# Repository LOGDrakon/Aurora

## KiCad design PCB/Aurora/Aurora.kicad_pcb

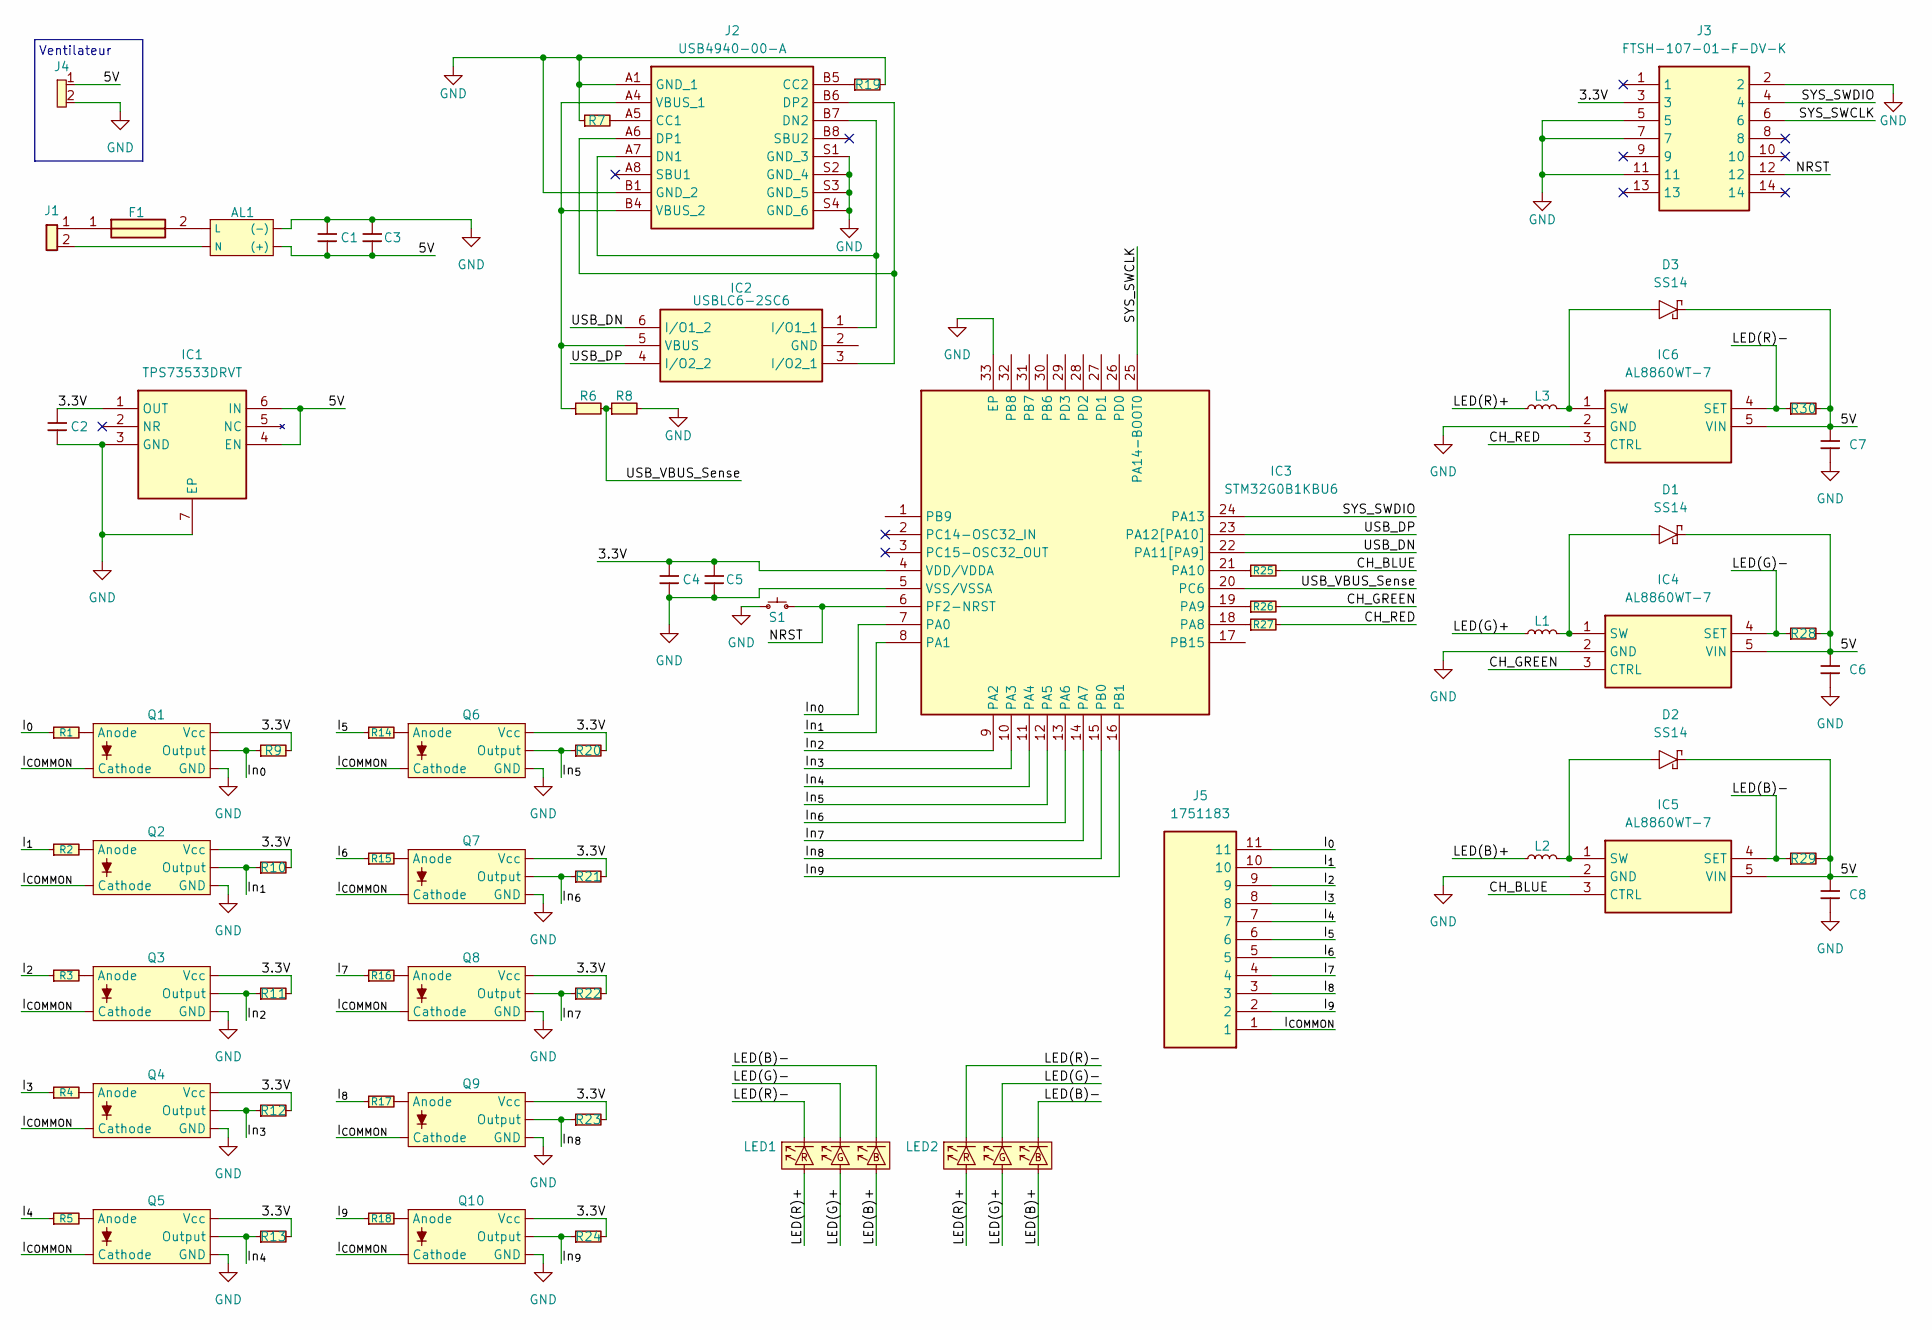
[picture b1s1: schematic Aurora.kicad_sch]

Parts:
AL1: PSK-10E-5; Parts Reference PSK-10E-5; Mouser No 490-PSK-10E-5
C1, C2, C4: GXT21BR71A475KE13L; CAPC2012X140N; Manufacturer_Part_Number GXT21BR71A475KE13L
C3: 100nF; C_0402_1005Metric; Parts Reference AC0402KRX7R7BB104
C5: 100nF; C_0402_1005Metric
C6, C7, C8: CGA4J1X7R0J106K125AC; CGA4J2NP01H223J125AA; Mouser Part Number 810-CGA4J1X7R0J106K
D1, D2, D3: SS14; DIOM5227X270N; Mouser Part Number 512-SS14
F1: 3403.0166.24; 3403016624; Mouser Part Number 693-3403.0166.24
IC1: TPS73533DRVT; SON65P200X200X80-7N; Mouser Part Number 595-TPS73533DRVT
IC2: USBLC6-2SC6; SOT95P280X145-6N; Mouser Part Number 511-USBLC6-2SC6
IC3: STM32G0B1KBU6; QFN-32-1EP_5x5mm_P0.5mm_EP3.45x3.45mm
IC4, IC5, IC6: AL8860WT-7; SOT95P280X100-5N; Mouser Part Number 621-AL8860WT-7
J1: 1190297; Mouser Part Number 651-1190297
J2: USB4940-00-A; USB494000A; Manufacturer_Part_Number USB4940-00-A
J3: FTSH-107-01-F-DV-K; FTSH-107-XX-YYY-DV-K; Mouser Part Number 200-FTSH10701FDVK
J4: 1190297; Pad_Connector_2; Mouser Part Number 651-1190297
J5: 1751183; Mouser Part Number 651-1751183
L1, L2, L3: PA4332.472NLT; PA4332472NLT; Mouser Part Number 673-PA4332472NLT
LED1, LED2: OT-3RGB-C30
Q1, Q2, Q3, Q4, Q5, Q6, Q7, Q8, Q9, Q10: TLP2303TPLE; Parts Reference TLP2303TPLE; Mouser No 757-TLP2303TPLE
R1, R2, R3, R4, R5, R14, R15, R16, R17, R18: 5.1R; RESC5025X120N; Mouser Part Number 279-35025K1FT
R6: MCT0603MC3302FP500; RESC1608X55N; Mouser Part Number 594-MCT0603MC3302FP5
R7, R19: CR0603-FX-5101ELF; RESC1608X55N; Mouser Part Number 652-CR0603FX-5101ELF
R8: ERJ-P08F8202V; ERJP08__1206_; Mouser Part Number 667-ERJ-P08F8202V
R9, R10, R11, R12, R13, R20, R21, R22, R23, R24: 3.3R; RESC1608X55N; Mouser Part Number 652-CR0603-FX3301ELF
R25, R26, R27: 100R; R_0603_1608Metric; Parts Reference SFR03EZPJ101; Mouser No 755-SFR03EZPJ101
R28, R29, R30: 0.16R; R_0603_1608Metric; Parts Reference RL0603FR-070R16L; Mouser No 603-RL0603FR-070R16L
S1: SPST; TS09-63-25-WT-160-SMT-TR; Parts Reference TS09-63-25-WT-160-SMT-TR; Mouser No 179-TS0925WT160SMTTR

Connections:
/3.3V: C2.1, C4.1, C5.1, IC1.1 (OUT), IC3.4 (VDD/VDDA), J3.3, Q1.6 (Vcc), Q2.6 (Vcc), Q3.6 (Vcc), Q4.6 (Vcc), Q5.6 (Vcc), Q6.6 (Vcc), Q7.6 (Vcc), Q8.6 (Vcc), Q9.6 (Vcc), Q10.6 (Vcc), R9.2, R10.2, R11.2, R12.2, R13.2, R20.2, R21.2, R22.2, R23.2, R24.2
/5V: AL1.4 ((+)), C1.2, C3.2, C6.1, C7.1, C8.1, D1.1, D2.1, D3.1, IC1.4 (EN), IC1.6 (IN), IC4.5 (VIN), IC5.5 (VIN), IC6.5 (VIN), J4.1, R28.2, R29.2, R30.2
/CH_BLUE: IC5.3 (CTRL), R25.2
/CH_GREEN: IC4.3 (CTRL), R26.2
/CH_RED: IC6.3 (CTRL), R27.2
/I_{0}: J5.11, R1.1
/I_{1}: J5.10, R2.1
/I_{2}: J5.9, R3.1
/I_{3}: J5.8, R4.1
/I_{4}: J5.7, R5.1
/I_{5}: J5.6, R14.1
/I_{6}: J5.5, R15.1
/I_{7}: J5.4, R16.1
/I_{8}: J5.3, R17.1
/I_{9}: J5.2, R18.1
/I_{COMMON}: J5.1, Q1.3 (Cathode), Q2.3 (Cathode), Q3.3 (Cathode), Q4.3 (Cathode), Q5.3 (Cathode), Q6.3 (Cathode), Q7.3 (Cathode), Q8.3 (Cathode), Q9.3 (Cathode), Q10.3 (Cathode)
/In_{0}: IC3.7 (PA0), Q1.5 (Output), R9.1
/In_{1}: IC3.8 (PA1), Q2.5 (Output), R10.1
/In_{2}: IC3.9 (PA2), Q3.5 (Output), R11.1
/In_{3}: IC3.10 (PA3), Q4.5 (Output), R12.1
/In_{4}: IC3.11 (PA4), Q5.5 (Output), R13.1
/In_{5}: IC3.12 (PA5), Q6.5 (Output), R20.1
/In_{6}: IC3.13 (PA6), Q7.5 (Output), R21.1
/In_{7}: IC3.14 (PA7), Q8.5 (Output), R22.1
/In_{8}: IC3.15 (PB0), Q9.5 (Output), R23.1
/In_{9}: IC3.16 (PB1), Q10.5 (Output), R24.1
/LED(B)+: L2.1, LED1.6, LED2.6
/LED(B)-: IC5.4 (SET), LED1.5, LED2.5, R29.1
/LED(G)+: L1.1, LED1.4, LED2.4
/LED(G)-: IC4.4 (SET), LED1.3, LED2.3, R28.1
/LED(R)+: L3.1, LED1.2, LED2.2
/LED(R)-: IC6.4 (SET), LED1.1, LED2.1, R30.1
/NRST: IC3.6 (PF2-NRST), J3.12, S1.2
/SYS_SWCLK: IC3.25 (PA14-BOOT0), J3.6
/SYS_SWDIO: IC3.24 (PA13), J3.4
/USB_DN: IC2.6 (I/O1_2), IC3.22 (PA11[PA9])
/USB_DP: IC2.4 (I/O2_2), IC3.23 (PA12[PA10])
/USB_VBUS_Sense: IC3.20 (PC6), R6.2, R8.1
GND: AL1.3 ((-)), C1.1, C2.2, C3.1, C4.2, C5.2, C6.2, C7.2, C8.2, IC1.3 (GND), IC1.7 (EP), IC3.5 (VSS/VSSA), IC3.33 (EP), IC4.2 (GND), IC5.2 (GND), IC6.2 (GND), J2.A1 (GND_1), J2.B1 (GND_2), J2.S1 (GND_3), J2.S2 (GND_4), J2.S3 (GND_5), J2.S4 (GND_6), J3.2, J3.5, J3.7, J3.11, J4.2, Q1.4 (GND), Q2.4 (GND), Q3.4 (GND), Q4.4 (GND), Q5.4 (GND), Q6.4 (GND), Q7.4 (GND), Q8.4 (GND), Q9.4 (GND), Q10.4 (GND), R7.1, R8.2, R19.2, S1.1
unnamed: AL1.1 (L), F1.2
unnamed: AL1.2 (N), J1.2, J1.4
unnamed: F1.1, J1.1, J1.3
unnamed: IC2.1 (I/O1_1), J2.A7 (DN1), J2.B7 (DN2)
unnamed: IC2.3 (I/O2_1), J2.A6 (DP1), J2.B6 (DP2)
unnamed: IC2.5 (VBUS), J2.A4 (VBUS_1), J2.B4 (VBUS_2), R6.1
unnamed: IC3.18 (PA8), R27.1
unnamed: IC3.19 (PA9), R26.1
unnamed: IC3.21 (PA10), R25.1
unnamed: D1.2, IC4.1 (SW), L1.2
unnamed: D2.2, IC5.1 (SW), L2.2
unnamed: D3.2, IC6.1 (SW), L3.2
unnamed: J2.A5 (CC1), R7.2
unnamed: J2.B5 (CC2), R19.1
unnamed: Q1.1 (Anode), R1.2
unnamed: Q2.1 (Anode), R2.2
unnamed: Q3.1 (Anode), R3.2
unnamed: Q4.1 (Anode), R4.2
unnamed: Q5.1 (Anode), R5.2
unnamed: Q6.1 (Anode), R14.2
unnamed: Q7.1 (Anode), R15.2
unnamed: Q8.1 (Anode), R16.2
unnamed: Q9.1 (Anode), R17.2
unnamed: Q10.1 (Anode), R18.2

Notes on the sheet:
Ventilateur

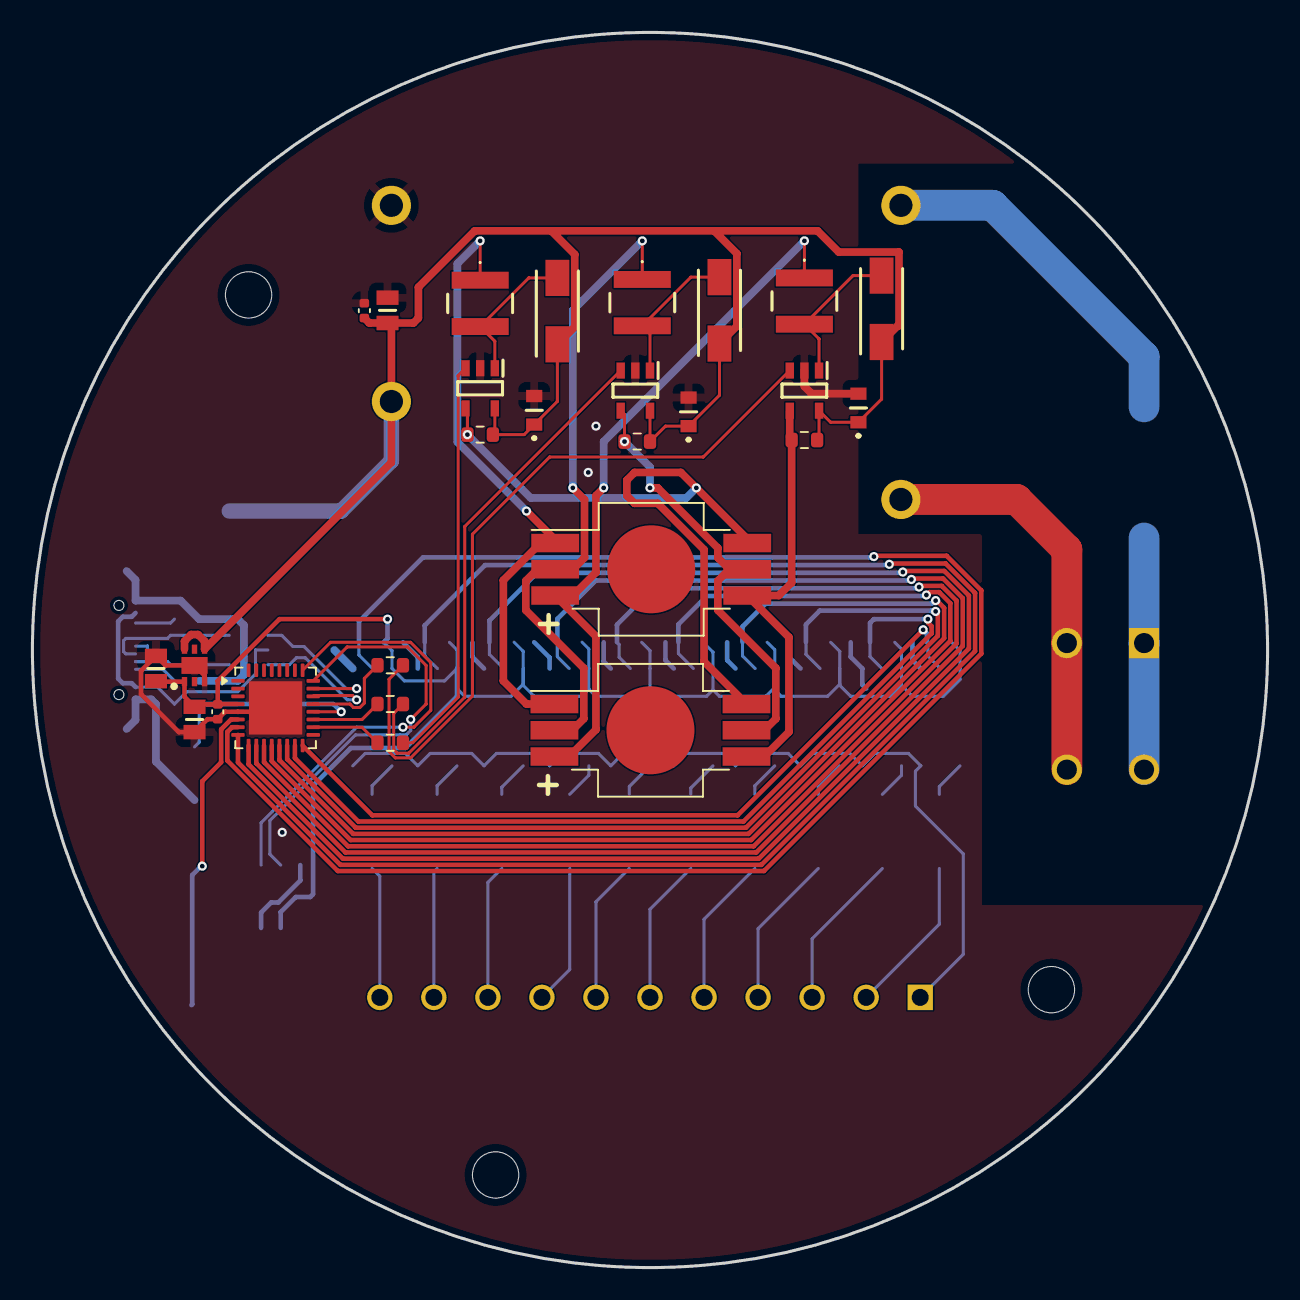
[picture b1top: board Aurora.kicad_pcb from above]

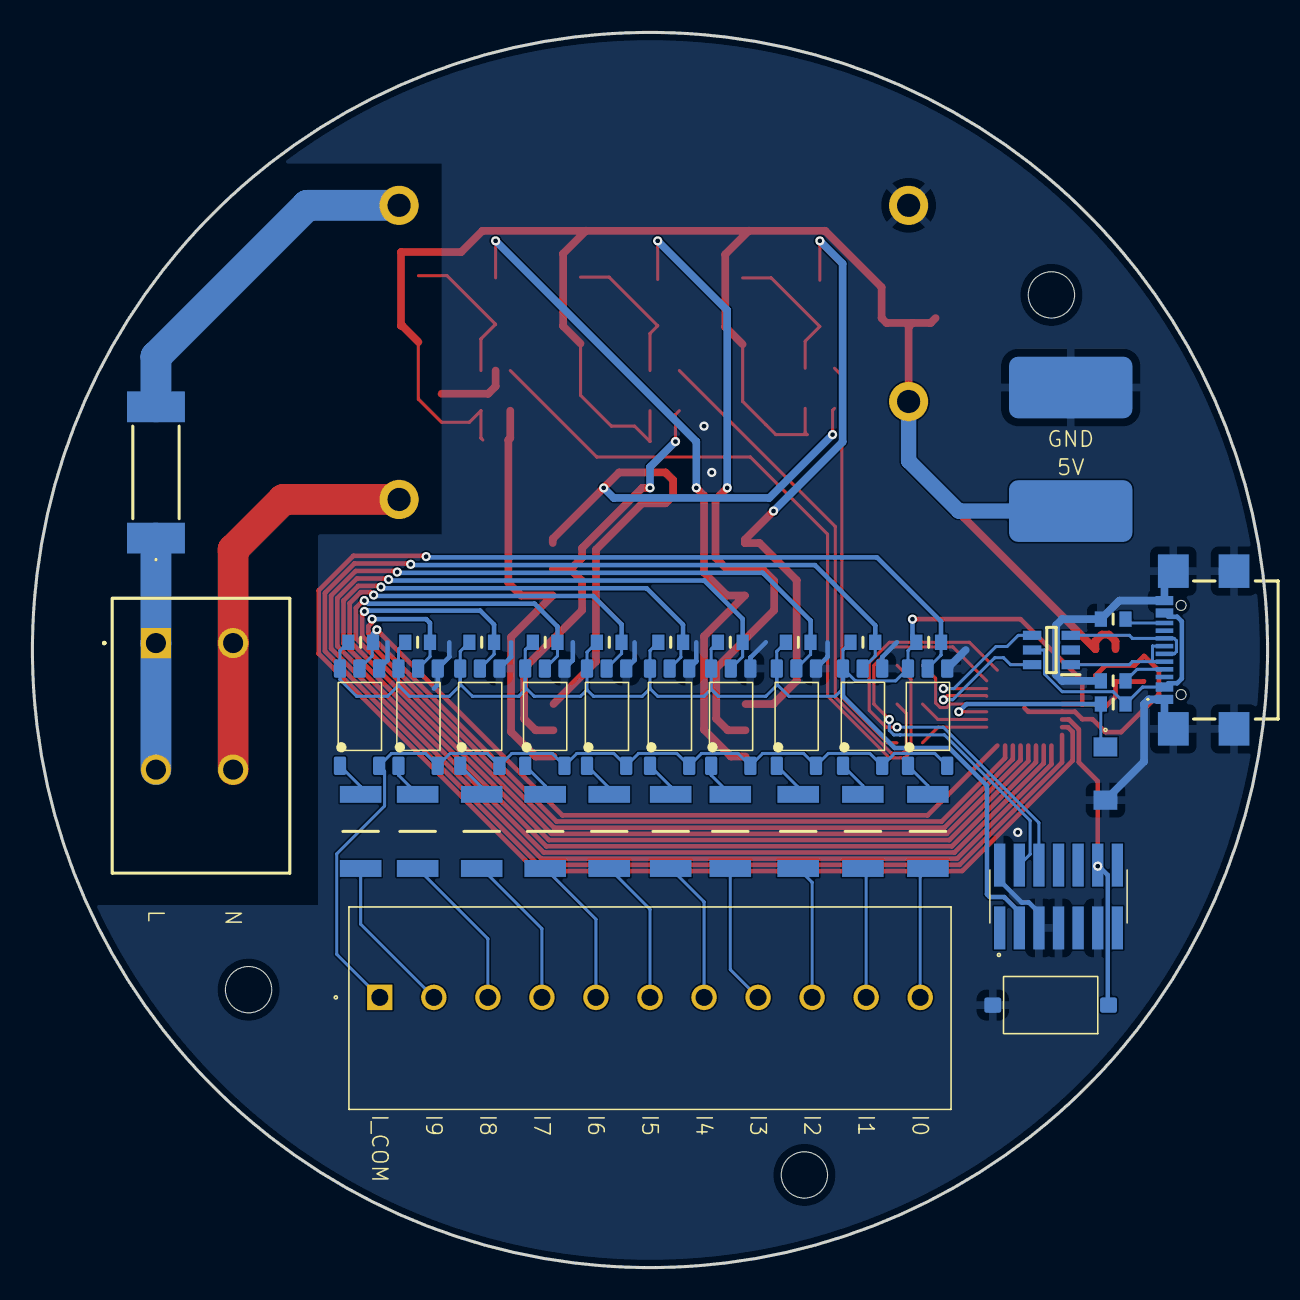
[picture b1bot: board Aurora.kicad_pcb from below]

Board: 2 copper layers, 80.0 x 80.0 mm, 70 parts (43 on the bottom side), 63 nets.

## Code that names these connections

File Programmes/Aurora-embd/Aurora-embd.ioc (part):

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Mcu.Name=STM32G0B1K(B-C-E)Ux
Mcu.Package=UFQFPN32
Mcu.UserName=STM32G0B1KBUx
PA0.GPIOParameters=GPIO_Label
PA0.GPIO_Label=I0
PA0.Signal=GPIO_Input
PA1.GPIOParameters=GPIO_Label
PA1.GPIO_Label=I1
PA1.Signal=GPIO_Input
PA10.Signal=S_TIM1_CH3
PA11\ [PA9].Mode=Device
PA11\ [PA9].Signal=USB_DM
PA12\ [PA10].Mode=Device
PA12\ [PA10].Signal=USB_DP
PA13.Mode=Serial_Wire
PA13.Signal=SYS_SWDIO
PA14-BOOT0.Mode=Serial_Wire
PA14-BOOT0.Signal=SYS_SWCLK
PA2.GPIOParameters=GPIO_Label
PA2.GPIO_Label=I2
PA2.Signal=GPIO_Input
PA3.GPIOParameters=GPIO_Label
PA3.GPIO_Label=I3
PA3.Signal=GPIO_Input
PA4.GPIOParameters=GPIO_Label
PA4.GPIO_Label=I4
PA4.Signal=GPIO_Input
PA5.GPIOParameters=GPIO_Label
PA5.GPIO_Label=I5
PA5.Signal=GPIO_Input
PA6.GPIOParameters=GPIO_Label
PA6.GPIO_Label=I6
PA6.Signal=GPIO_Input
PA7.GPIOParameters=GPIO_Label
PA7.GPIO_Label=I7
PA7.Signal=GPIO_Input
PA8.Signal=S_TIM1_CH1
PA9.Signal=S_TIM1_CH2
PB0.GPIOParameters=GPIO_Label
PB0.GPIO_Label=I8
PB0.Signal=GPIO_Input
PB1.GPIOParameters=GPIO_Label
PB1.GPIO_Label=I9
PB1.Signal=GPIO_Input
PC6.GPIOParameters=GPIO_Label
PC6.GPIO_Label=VBUS_Sense
PC6.Signal=GPIO_Input
RCC.HSE_VALUE=8000000
RCC.SYSCLKFreq_VALUE=16000000
board=custom

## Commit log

2026-03-30 Schema + PCB
